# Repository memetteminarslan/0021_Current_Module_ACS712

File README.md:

# 0021_Current_Module_ACS712
You are seeing a large number of widely used current modules in electronic development kits. More information coming soon...

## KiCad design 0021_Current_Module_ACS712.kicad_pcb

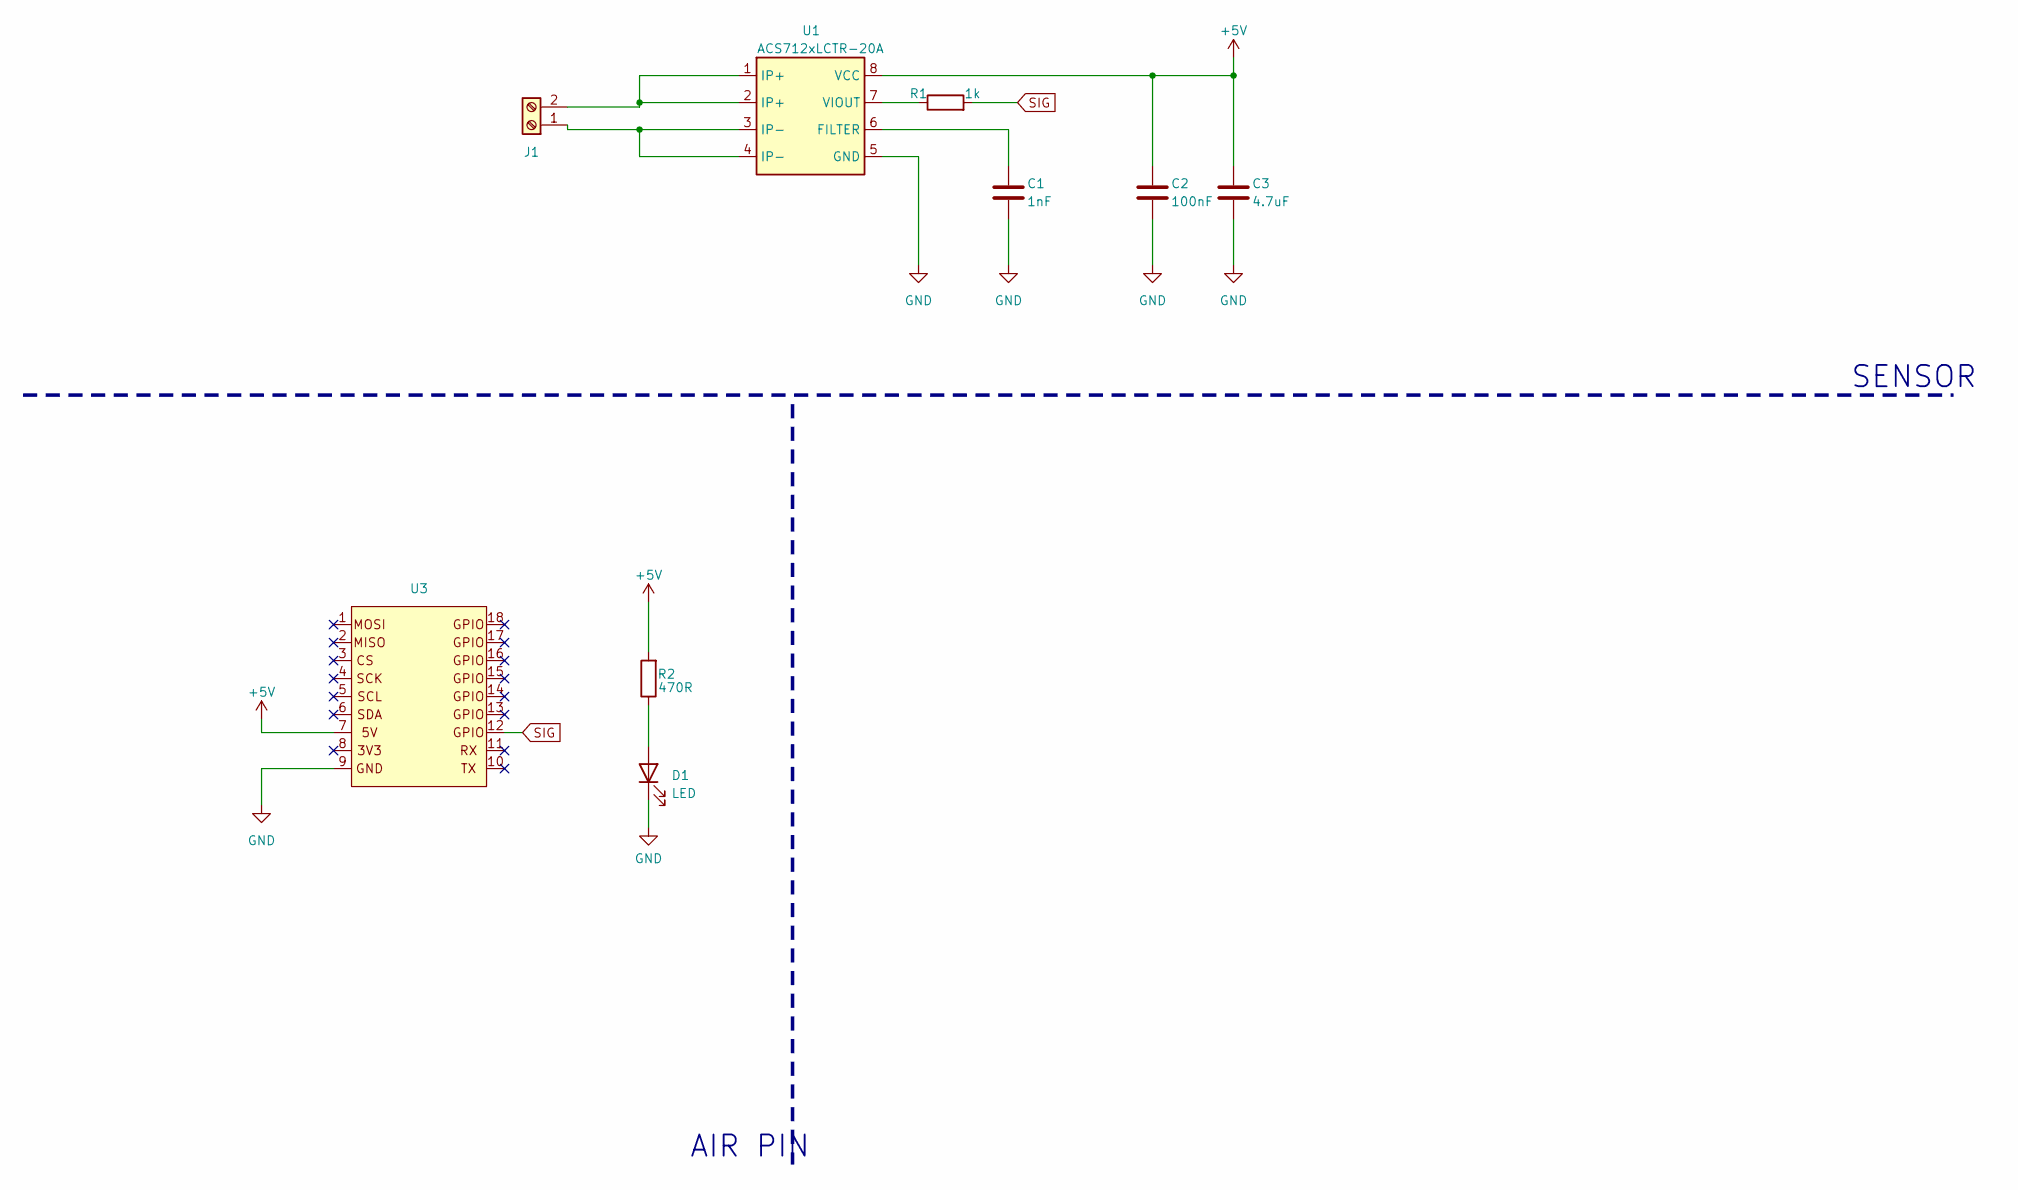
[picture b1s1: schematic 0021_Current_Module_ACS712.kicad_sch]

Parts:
C1: 1nF; C_0805_2012Metric
C2: 100nF; C_0805_2012Metric
C3: 4.7uF; C_0805_2012Metric
D1: LED; LED_0805_2012Metric
J1: Screw_Terminal_01x02; barriyer_7.62
R1: 1k; R_0805_2012Metric
R2: 470R; R_0805_2012Metric
U1: ACS712xLCTR-20A; SOIC-8_3.9x4.9mm_P1.27mm
U3: pin_header

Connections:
+5V: C2.1, C3.1, R2.2, U1.8 (VCC), U3.7
GND: C1.2, C2.2, C3.2, D1.1 (K), U1.5 (GND), U3.9
unnamed: D1.2 (A), R2.1
unnamed: J1.1, U1.3 (IP-), U1.4 (IP-)
unnamed: J1.2, U1.1 (IP+), U1.2 (IP+)
unnamed: C1.1, U1.6 (FILTER)
unnamed: R1.1, U1.7 (VIOUT)
SIG: R1.2, U3.12

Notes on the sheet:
SENSOR
AIR PIN

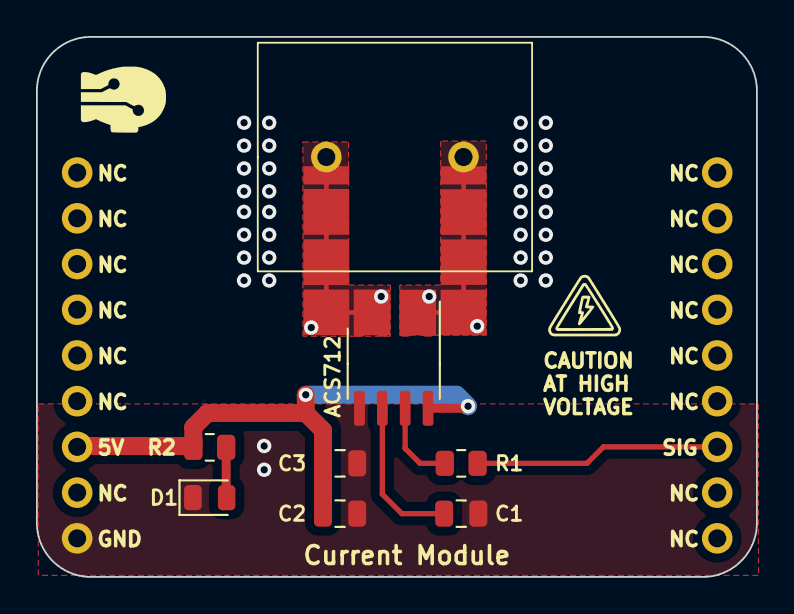
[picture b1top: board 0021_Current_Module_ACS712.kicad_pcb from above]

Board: 2 copper layers, 40.0 x 30.0 mm, 9 parts (0 on the bottom side), 8 nets.
